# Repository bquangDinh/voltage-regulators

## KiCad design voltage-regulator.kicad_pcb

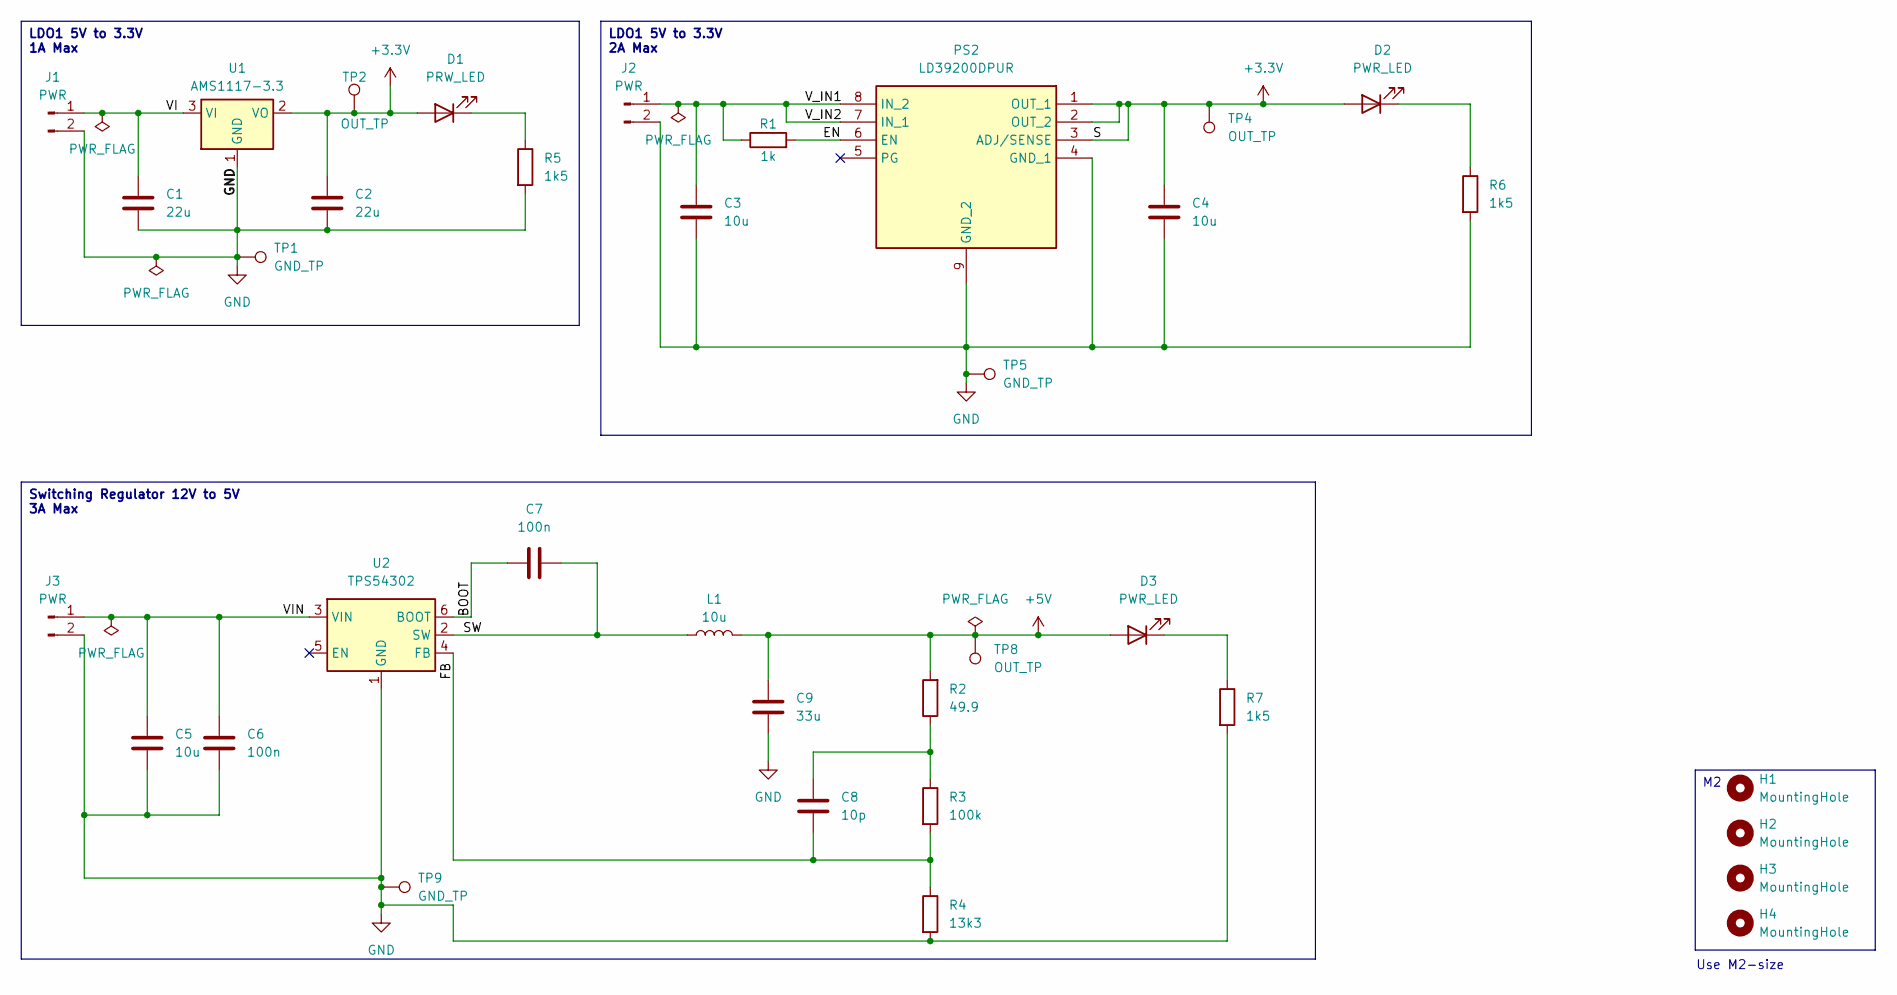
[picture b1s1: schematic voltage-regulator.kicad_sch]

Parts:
C1, C2: 22u; C_0805_2012Metric
C3, C4, C5: 10u; C_0603_1608Metric
C6, C7: 100n; C_0402_1005Metric
C8: 10p; C_0402_1005Metric
C9: 33u; C_0805_2012Metric
D1: PRW_LED; LED_0603_1608Metric
D2, D3: PWR_LED; LED_0603_1608Metric
H1, H2, H3, H4: MountingHole; MountingHole_2.2mm_M2
J1, J2, J3: PWR; PinHeader_1x02_P2.54mm_Vertical
L1: 10u; INDPM6965X300N
PS2: LD39200DPUR; SON80P400X400X100-9N-D; Mouser Part Number 511-LD39200DPUR
R1: 1k; R_0402_1005Metric
R2: 49.9; R_0402_1005Metric
R3: 100k; R_0603_1608Metric
R4: 13k3; R_0402_1005Metric
R5, R6, R7: 1k5; R_0402_1005Metric
TP1, TP5, TP9: GND_TP; Pin_D1.0mm_L10.0mm
TP2, TP4, TP8: OUT_TP; Pin_D1.0mm_L10.0mm
U1: AMS1117-3.3; SOT-223-3_TabPin2
U2: TPS54302; SOT-23-6

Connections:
+3.3V: C2.2, C4.2, D1.2 (A), D2.2 (A), PS2.1 (OUT_1), PS2.2 (OUT_2), PS2.3 (ADJ/SENSE), TP2.1, TP4.1, U1.2 (VO)
+5V: C9.2, D3.2 (A), L1.2, R2.2, TP8.1
/BOOT: C7.1, U2.6 (BOOT)
/EN: PS2.6 (EN), R1.2
/FB: C8.2, R3.2, R4.1, U2.4 (FB)
/SW: C7.2, L1.1, U2.2 (SW)
/VI: C1.2, J1.1, U1.3 (VI)
/VIN: C5.1, C6.1, J3.1, U2.3 (VIN)
/V_IN1: C3.2, J2.1, PS2.7 (IN_1), PS2.8 (IN_2), R1.1
GND: C1.1, C2.1, C3.1, C4.1, C5.2, C6.2, C9.1, J1.2, J2.2, J3.2, PS2.4 (GND_1), PS2.9 (GND_2), R4.2, R5.2, R6.2, R7.2, TP1.1, TP5.1, TP9.1, U1.1 (GND), U2.1 (GND)
unnamed: C8.1, R2.1, R3.1
unnamed: D1.1 (K), R5.1
unnamed: D2.1 (K), R6.1
unnamed: D3.1 (K), R7.1

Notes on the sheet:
Use M2-size
LDO1 5V to 3.3V 1A Max
Switching Regulator 12V to 5V 3A Max
LDO1 5V to 3.3V 2A Max

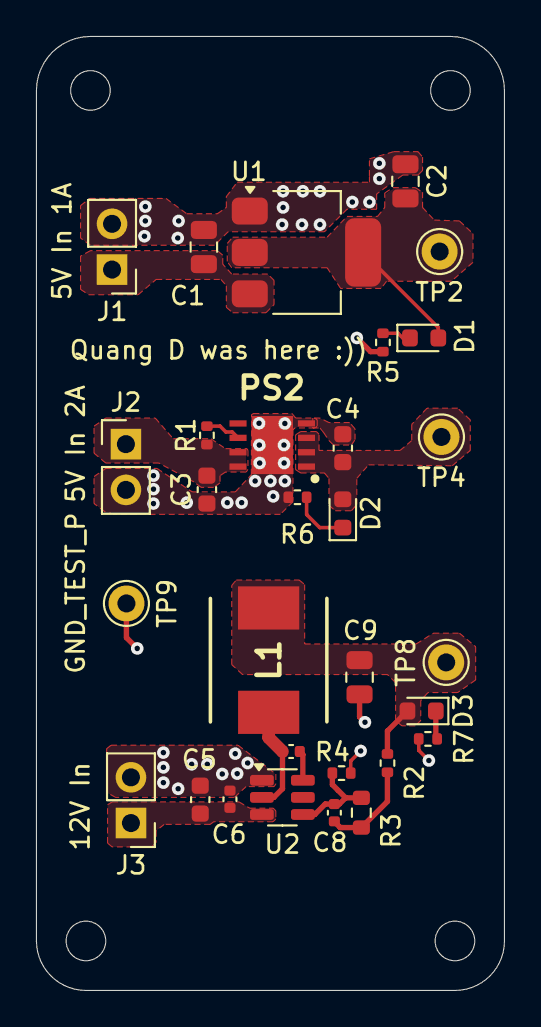
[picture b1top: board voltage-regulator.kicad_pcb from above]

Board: 2 copper layers, 26.0 x 53.0 mm, 34 parts (0 on the bottom side), 14 nets.

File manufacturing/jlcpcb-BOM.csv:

Comment,Designator,Footprint,JLCPCB Part # (optional)
22u,"C1,C2",Capacitor_SMD:C_0805_2012Metric,
10u,"C3,C4,C5",Capacitor_SMD:C_0603_1608Metric,
100n,"C6,C7",Capacitor_SMD:C_0402_1005Metric,
10p,C8,Capacitor_SMD:C_0402_1005Metric,
33u,C9,Capacitor_SMD:C_0805_2012Metric,
PRW_LED,D1,LED_SMD:LED_0603_1608Metric,
PWR_LED,"D2,D3",LED_SMD:LED_0603_1608Metric,
PWR,"J1,J2,J3",Connector_PinHeader_2.54mm:PinHeader_1x02_P2.54mm_Vertical,
10u,L1,Inductor_SMD:L_0805_2012Metric,
LD39200DPUR,PS2,SamacSys_Parts:SON80P400X400X100-9N-D,https://componentsearchengine.com/Datasheets/1/LD39200DPUR.pdf
1k,R1,Resistor_SMD:R_0402_1005Metric,
49.9,R2,Resistor_SMD:R_0402_1005Metric,
100k,R3,Resistor_SMD:R_0603_1608Metric,
13k3,R4,Resistor_SMD:R_0402_1005Metric,
1k5,"R5,R6,R7",Resistor_SMD:R_0402_1005Metric,
OUT_TP,"TP2,TP4,TP8",Connector_Pin:Pin_D1.0mm_L10.0mm,
AMS1117-3.3,U1,Package_TO_SOT_SMD:SOT-223-3_TabPin2,http://www.advanced-monolithic.com/pdf/ds1117.pdf
TPS54302,U2,Package_TO_SOT_SMD:SOT-23-6,http://www.ti.com/lit/ds/symlink/tps54302.pdf
GND_TP,TP9,Connector_Pin:Pin_D1.0mm_L10.0mm,

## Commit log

2025-10-08 Added switching regulator
2025-10-25 Added changes
2025-11-14 Changes things
